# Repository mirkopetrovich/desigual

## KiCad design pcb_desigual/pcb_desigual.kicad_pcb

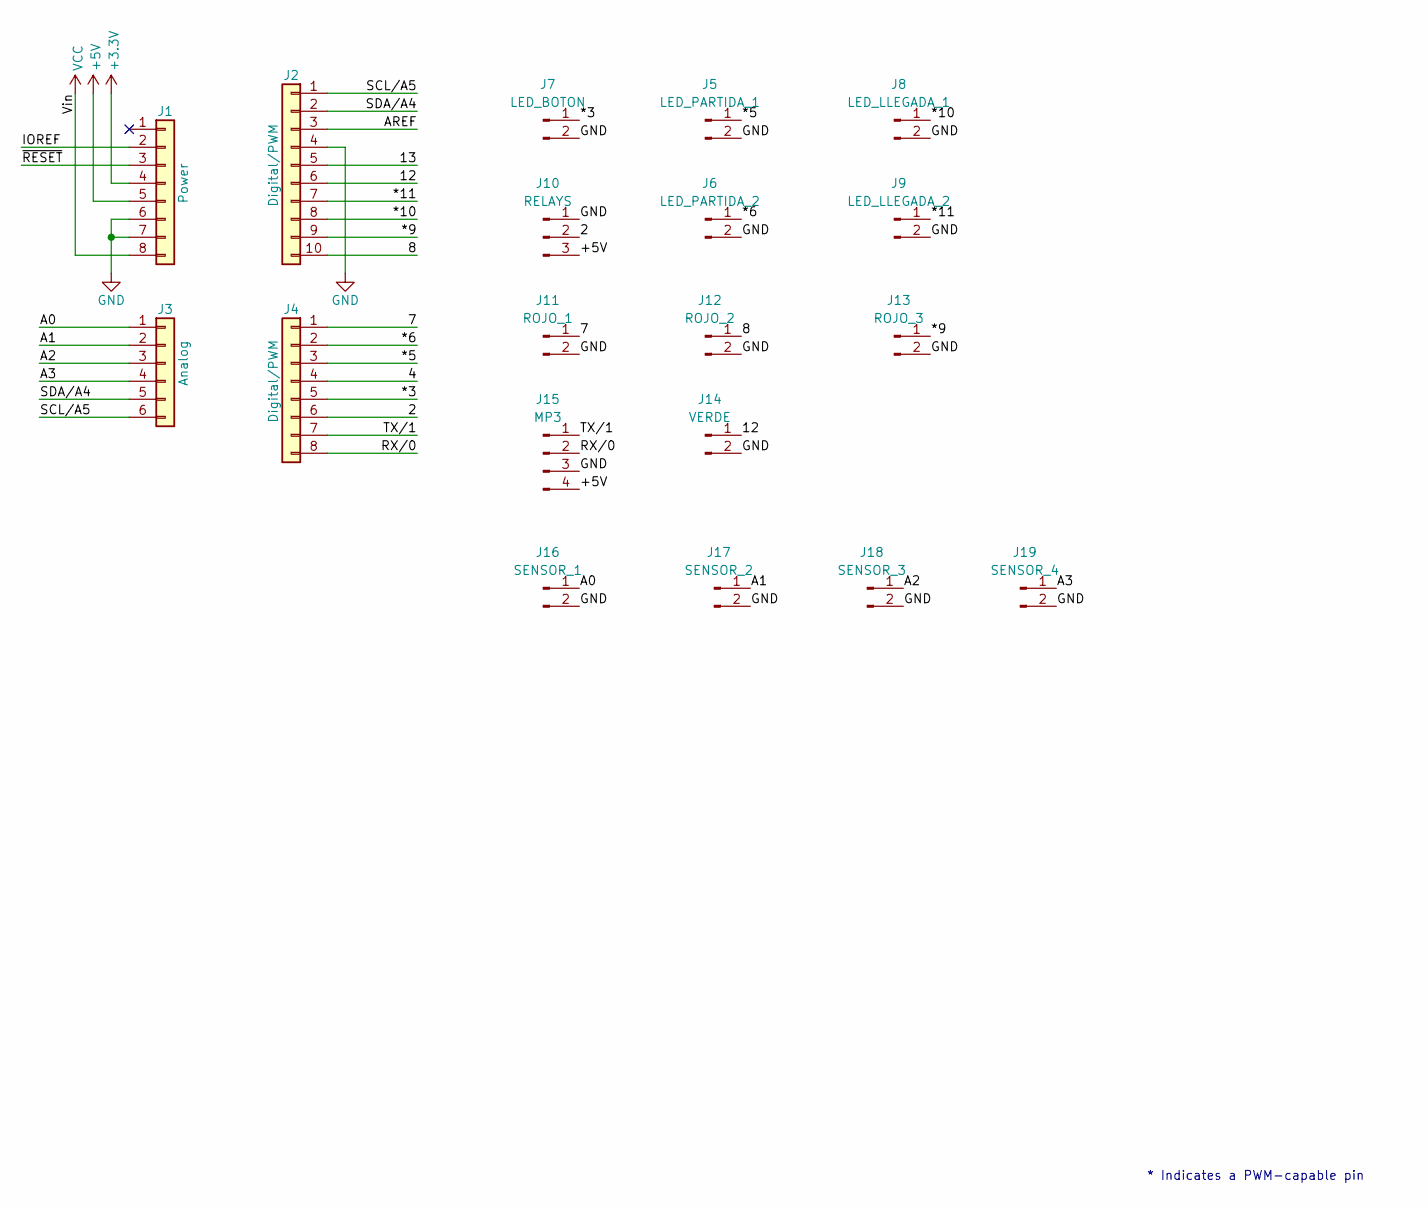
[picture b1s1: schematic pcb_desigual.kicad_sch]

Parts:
J1: Power; PinSocket_1x08_P2.54mm_Vertical
J2: Digital/PWM; PinSocket_1x10_P2.54mm_Vertical
J3: Analog; PinSocket_1x06_P2.54mm_Vertical
J4: Digital/PWM; PinSocket_1x08_P2.54mm_Vertical
J5: LED_PARTIDA_1; PinHeader_1x02_P2.54mm_Vertical
J6: LED_PARTIDA_2; PinHeader_1x02_P2.54mm_Vertical
J7: LED_BOTON; PinHeader_1x02_P2.54mm_Vertical
J8: LED_LLEGADA_1; PinHeader_1x02_P2.54mm_Vertical
J9: LED_LLEGADA_2; PinHeader_1x02_P2.54mm_Vertical
J10: RELAYS; PinHeader_1x03_P2.54mm_Vertical
J11: ROJO_1; PinHeader_1x02_P2.54mm_Vertical
J12: ROJO_2; PinHeader_1x02_P2.54mm_Vertical
J13: ROJO_3; PinHeader_1x02_P2.54mm_Vertical
J14: VERDE; PinHeader_1x02_P2.54mm_Vertical
J15: MP3; PinHeader_1x04_P2.54mm_Vertical
J16: SENSOR_1; PinHeader_1x02_P2.54mm_Vertical
J17: SENSOR_2; PinHeader_1x02_P2.54mm_Vertical
J18: SENSOR_3; PinHeader_1x02_P2.54mm_Vertical
J19: SENSOR_4; PinHeader_1x02_P2.54mm_Vertical

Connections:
+3V3: J1.4
+5V: J1.5, J10.3, J15.4
/2: J4.6, J10.2
/4: J4.4
/7: J4.1, J11.1
/8: J2.10, J12.1
/12: J2.6, J14.1
/13: J2.5
/*3: J4.5, J7.1
/*5: J4.3, J5.1
/*6: J4.2, J6.1
/*9: J2.9, J13.1
/*10: J2.8, J8.1
/*11: J2.7, J9.1
/A0: J3.1, J16.1
/A1: J3.2, J17.1
/A2: J3.3, J18.1
/A3: J3.4, J19.1
/AREF: J2.3
/IOREF: J1.2
/RX/0: J4.8, J15.2
/SCL/A5: J2.1, J3.6
/SDA/A4: J2.2, J3.5
/TX/1: J4.7, J15.1
/~RESET: J1.3
GND: J1.6, J1.7, J2.4, J5.2, J6.2, J7.2, J8.2, J9.2, J10.1, J11.2, J12.2, J13.2, J14.2, J15.3, J16.2, J17.2, J18.2, J19.2
VCC: J1.8

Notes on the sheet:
* Indicates a PWM-capable pin

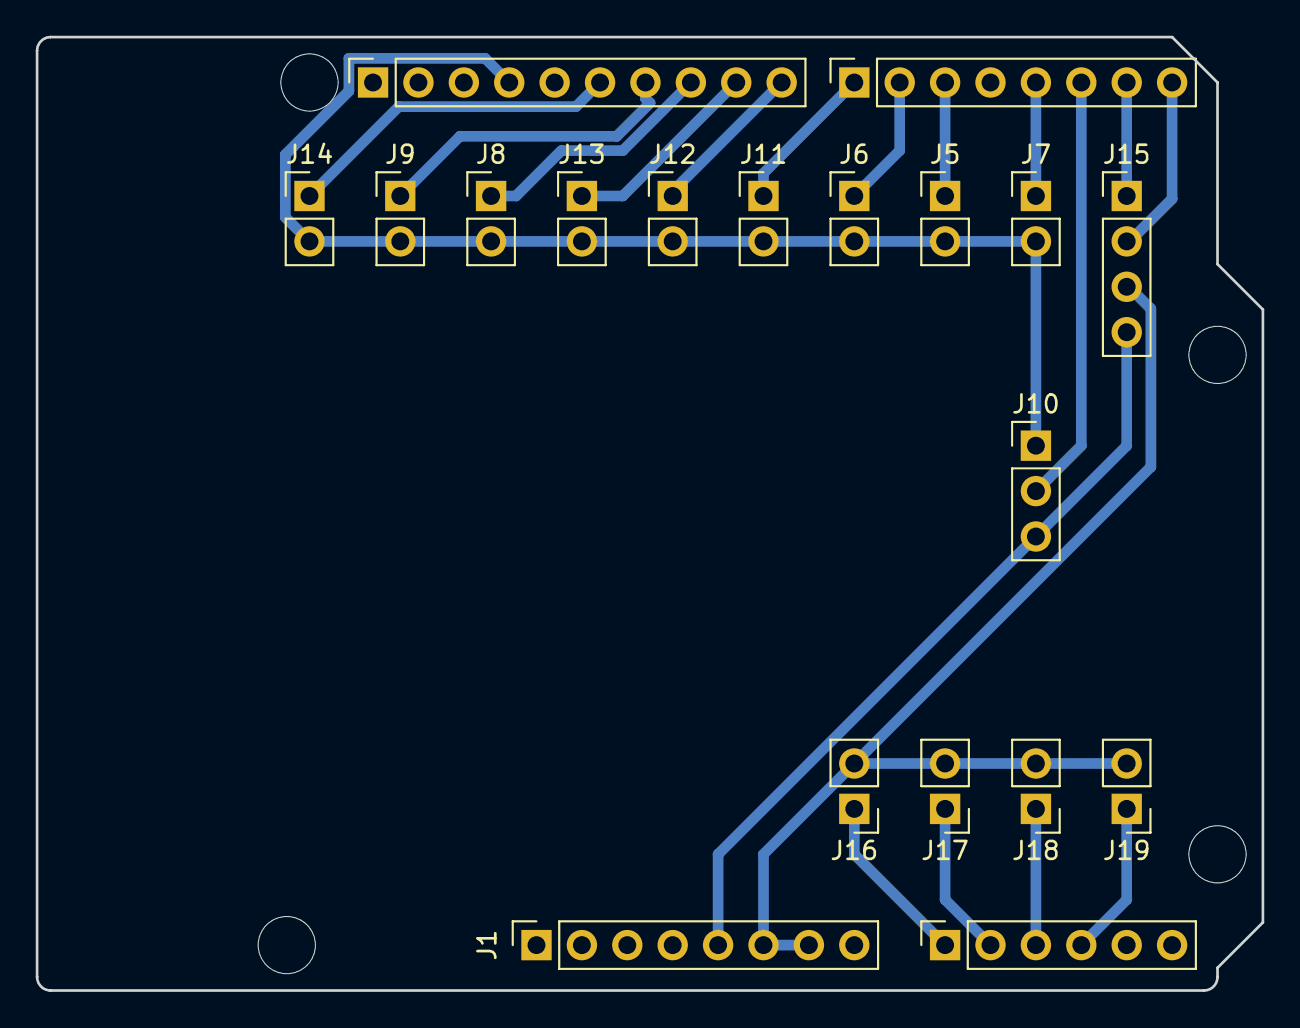
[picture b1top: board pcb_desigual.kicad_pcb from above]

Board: 2 copper layers, 68.6 x 53.3 mm, 23 parts (0 on the bottom side), 20 nets.

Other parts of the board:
MH1, MH2, MH3, MH4: MountingHole_3.2mm

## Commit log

2023-12-21 sketch + patch + pcb + dfplayer
